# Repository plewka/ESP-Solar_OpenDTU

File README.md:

# ESP-Solar_OpenDTU
PCB for OpenDTU in Cable Branchbox, LineSupply w. Fuses, RS485/RS232-Olimex, Relais, DS2485 OneWire, I2C-Header...

Mechanically fits into quite compact HNS 989861-H01 wiring box (form closure only).
If not all features are used, even edged Wieland-Socket should fit.
LEDs need LightGuides: no. position-drawing and not included in material list 

Tradeoff: Very limited space, copyrighted code for ds2485

image::ESP-SolarV1.jpg

* WESP32-WROOM-based (internal or external antenna)

* 5x20 Fuseholder (Supply)
* Varistor
* HiLink Supplymodule f.e. 230V->3.3V

* 5x20 Fuseholder (Relais)
* Relais SANYOU 10A

* modern 1Wire-Controler DS2485
* programming Header (Shelly-Pinout)
* I2C+VCC+GND header
* 2x5 Ribbon Connector for Olimex' RS485/RS232-Modules
* LEDs (green: power, red:active, or:DS2485 GPIO)

* TTL serial connector f.e. for IR-Energy reading 
* robust cage clamps for external connections

The board was done for differend scenarios including HoymilesDTU, using different RF-Modules,
reading the new IR-Energy counters with "Volkszähler", measure distributed temerature locations 
with OneWire-Sensors and control of pool pump or heating elements, maybe some IR motion detection 
in the garage, interfacing RS485/Modbus/RS232 for Solar-Inverters etc. - CAN- and metering bus 
are missing, though.

Would be great to hear how you used it or modified it for!

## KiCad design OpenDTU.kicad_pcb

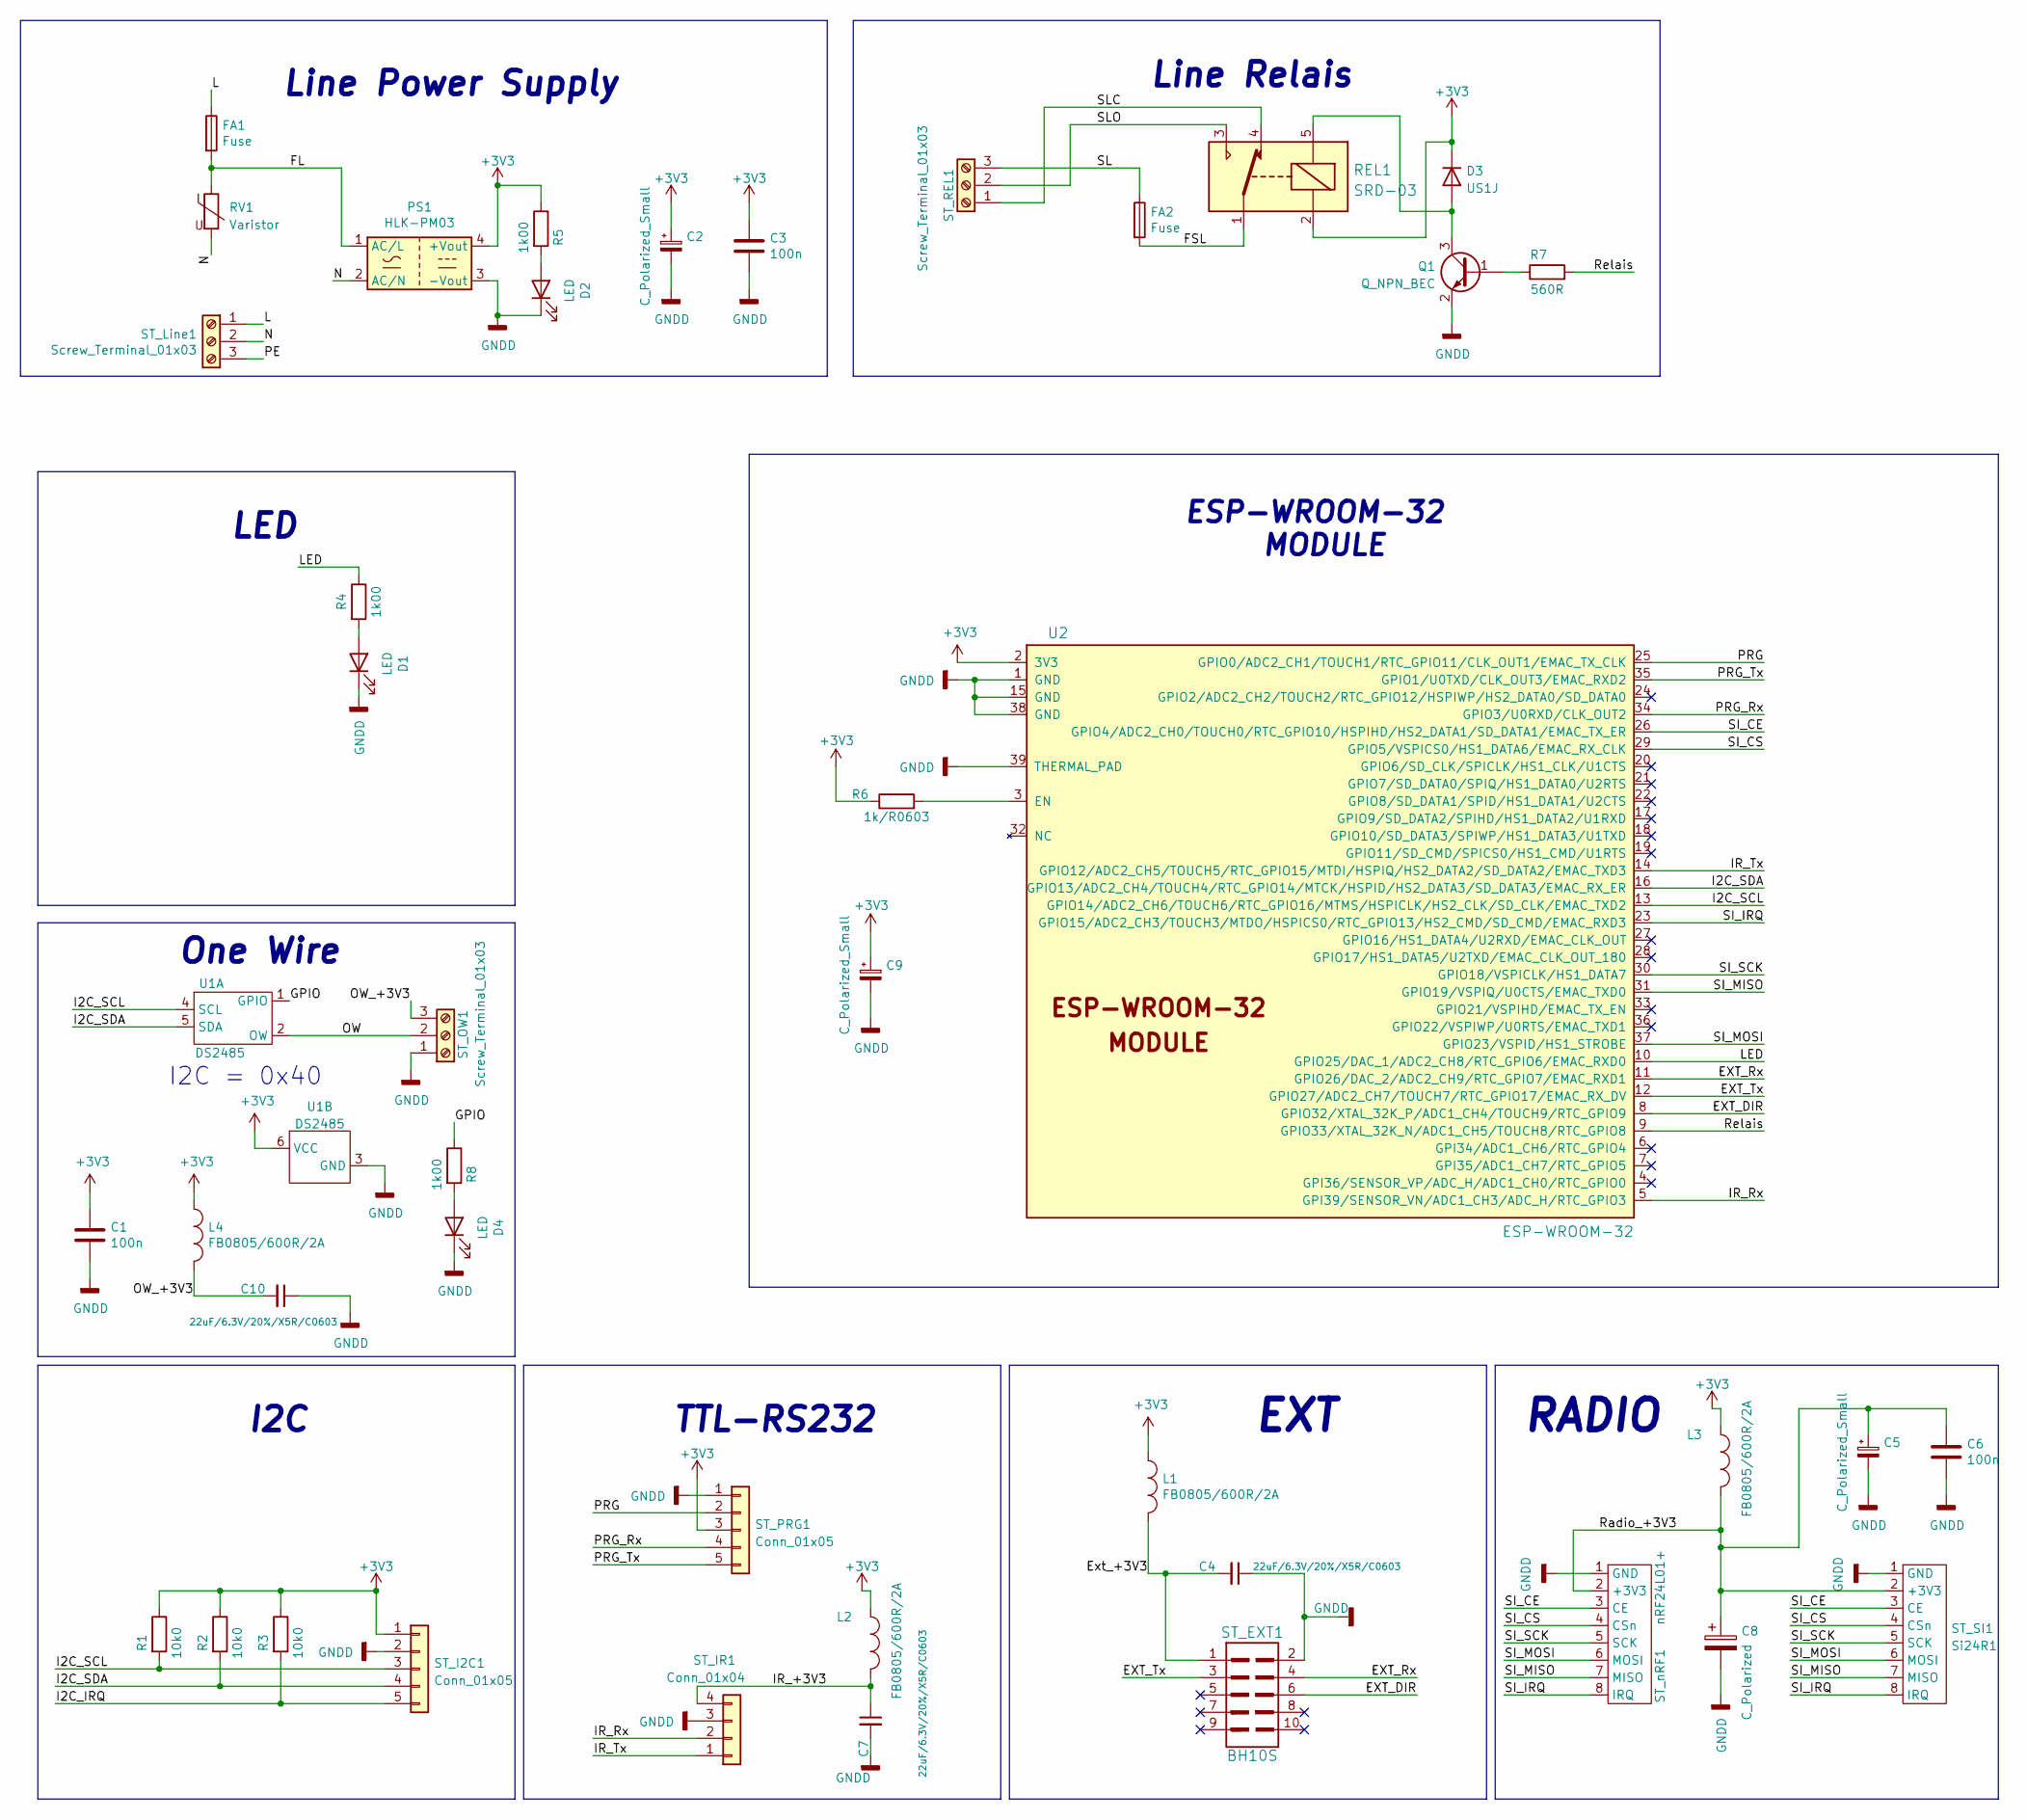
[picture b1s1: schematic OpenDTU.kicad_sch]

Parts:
C1, C3, C6: 100n; C_0603_1608Metric
C2, C5, C9: C_Polarized_Small; CP_EIA-3528-12_Kemet-T
C4, C7, C10: 22uF/6.3V/20%/X5R/C0603; C_0603_1608Metric
C8: C_Polarized; CP_EIA-7260-38_AVX-R
D1, D2, D4: LED; LED_D3.0mm_Clear
D3: US1J; D_SMA
FA1, FA2: Fuse; Fuseholder_Cylinder-5x20mm_Bulgin_FX0456_Vertical_Closed
L1, L2, L3, L4: FB0805/600R/2A; L_0805_2012Metric
PS1: HLK-PM03; Converter_ACDC_HiLink_HLK-PMxx
Q1: Q_NPN_BEC; SOT-23
R1, R2, R3: 10k0; R_0603_1608Metric
R4, R5, R8: 1k00; R_0603_1608Metric
R6: 1k/R0603; R_0603_1608Metric
R7: 560R; R_0603_1608Metric
REL1: SRD-03; Relay_SPDT_SANYOU_SRD_Series_Form_C
RV1: Varistor; RV_Disc_D12mm_W4.2mm_P7.5mm
ST_EXT1: BH10S; PinHeader_2x05_P2.54mm_Vertical
ST_I2C1: Conn_01x05; PinSocket_1x05_P2.54mm_Vertical
ST_IR1: Conn_01x04; TerminalBlock_WAGO_236-404_1x04_P5.00mm_45Degree
ST_Line1: Screw_Terminal_01x03; TerminalBlock_WAGO_236-403_1x03_P5.00mm_45Degree
ST_OW1: Screw_Terminal_01x03; TerminalBlock_WAGO_236-403_1x03_P5.00mm_45Degree
ST_PRG1: Conn_01x05; PinHeader_1x05_P2.54mm_Vertical
ST_REL1: Screw_Terminal_01x03; TerminalBlock_WAGO_236-403_1x03_P5.00mm_45Degree
ST_SI1: Si24R1; PinSocket_1x08_P1.27mm_Vertical
ST_nRF1: nRF24L01+; PinHeader_2x04_P2.54mm_Vertical
U1: DS2485; DFN-6-1EP_3x3mm_P0.95mm_EP1.7x2.6mm
U2: ESP-WROOM-32; ESP32-WROOM-32E

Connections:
+3V3: C1.1, C2.1, C3.1, C9.1, D3.1 (K), L1.1, L2.1, L3.1, L4.1, PS1.4 (+Vout), R1.1, R2.1, R3.1, R5.1, R6.1, REL1.2, ST_I2C1.1, ST_PRG1.3, U1.6 (VCC), U2.2 (3V3)
/EXT_DIR: ST_EXT1.6, U2.8 (GPIO32/XTAL_32K_P/ADC1_CH4/TOUCH9/RTC_G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)
/EXT_Rx: ST_EXT1.4, U2.11 (GPIO26/DAC_2/ADC2_CH9/RTC_GPIO7/EMAC_RX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)
/EXT_Tx: ST_EXT1.3, U2.12 (GPIO27/ADC2_CH7/TOUCH7/RTC_GPIO17/EMAC_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)
/Ext_+3V3: C4.2, L1.2, ST_EXT1.1
/FL: FA1.2, PS1.1 (AC/L), RV1.1
/FSL: FA2.2, REL1.1
/GPIO: R8.1, U1.1 (GPIO)
/I2C_IRQ: R3.2, ST_I2C1.5
/I2C_SCL: R1.2, ST_I2C1.3, U1.4 (SCL), U2.13 (GPIO14/ADC2_CH6/TOUCH6/RTC_GPIO16/MTMS/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)
/I2C_SDA: R2.2, ST_I2C1.4, U1.5 (SDA), U2.16 (GPIO13/ADC2_CH4/TOUCH4/RTC_GPIO14/MTCK/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)
/IR_+3V3: C7.1, L2.2, ST_IR1.4
/IR_Rx: ST_IR1.2, U2.5 (GPI39/SENSOR_VN/ADC1_CH3/ADC_H/RTC_GPIO3)
/IR_Tx: ST_IR1.1, U2.14 (GPIO12/ADC2_CH5/TOUCH5/RTC_GPIO15/MTDI/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)
/L: FA1.1, ST_Line1.1
/LED: R4.1, U2.10 (GPIO25/DAC_1/ADC2_CH8/RTC_GPIO6/EMAC_RX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)
/N: PS1.2 (AC/N), RV1.2, ST_Line1.2
/OW: ST_OW1.2, U1.2 (OW)
/OW_+3V3: C10.2, L4.2, ST_OW1.3
/PE: ST_Line1.3
/PRG: ST_PRG1.2, U2.25 (GPIO0/ADC2_CH1/TOUCH1/RTC_GPIO11/CLK_OU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)
/PRG_Rx: ST_PRG1.4, U2.34 (GPIO3/U0RXD/CLK_OUT2)
/PRG_Tx: ST_PRG1.5, U2.35 (GPIO1/U0TXD/CLK_OUT3/EMAC_RXD2)
/Radio_+3V3: C5.1, C6.1, C8.1, L3.2, ST_SI1.2 (+3V3), ST_nRF1.2 (+3V3)
/Relais: R7.2, U2.9 (GPIO33/XTAL_32K_N/ADC1_CH5/TOUCH8/RTC_G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)
/SI_CE: ST_SI1.3 (CE), ST_nRF1.3 (CE), U2.26 (GPIO4/ADC2_CH0/TOUCH0/RTC_GPIO10/HSPIHD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)
/SI_CS: ST_SI1.4 (CSn), ST_nRF1.4 (CSn), U2.29 (GPIO5/VSPICS0/HS1_DATA6/EMAC_RX_CLK)
/SI_IRQ: ST_SI1.8 (IRQ), ST_nRF1.8 (IRQ), U2.23 (GPIO15/ADC2_CH3/TOUCH3/MTDO/HSPICS0/RTC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)
/SI_MISO: ST_SI1.7 (MISO), ST_nRF1.7 (MISO), U2.31 (GPIO19/VSPIQ/U0CTS/EMAC_TXD0)
/SI_MOSI: ST_SI1.6 (MOSI), ST_nRF1.6 (MOSI), U2.37 (GPIO23/VSPID/HS1_STROBE)
/SI_SCK: ST_SI1.5 (SCK), ST_nRF1.5 (SCK), U2.30 (GPIO18/VSPICLK/HS1_DATA7)
/SL: FA2.1, ST_REL1.3
/SLC: REL1.4, ST_REL1.1
/SLO: REL1.3, ST_REL1.2
GNDD: C1.2, C2.2, C3.2, C4.1, C5.2, C6.2, C7.2, C8.2, C9.2, C10.1, D1.1 (K), D2.1 (K), D4.1 (K), PS1.3 (-Vout), Q1.2 (E), ST_EXT1.2, ST_I2C1.2, ST_IR1.3, ST_OW1.1, ST_PRG1.1, ST_SI1.1 (GND), ST_nRF1.1 (GND), U1.3 (GND), U2.1 (GND), U2.15 (GND), U2.38 (GND), U2.39 (THERMAL_PAD)
unnamed: D1.2 (A), R4.2
unnamed: D2.2 (A), R5.2
unnamed: D3.2 (A), Q1.3 (C), REL1.5
unnamed: D4.2 (A), R8.2
unnamed: Q1.1 (B), R7.1
unnamed: R6.2, U2.3 (EN)

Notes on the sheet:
I2C = 0x40
Line Relais
LED
EXT
ESP-WROOM-32 MODULE
RADIO
I2C
Line Power Supply
One Wire
TTL-RS232

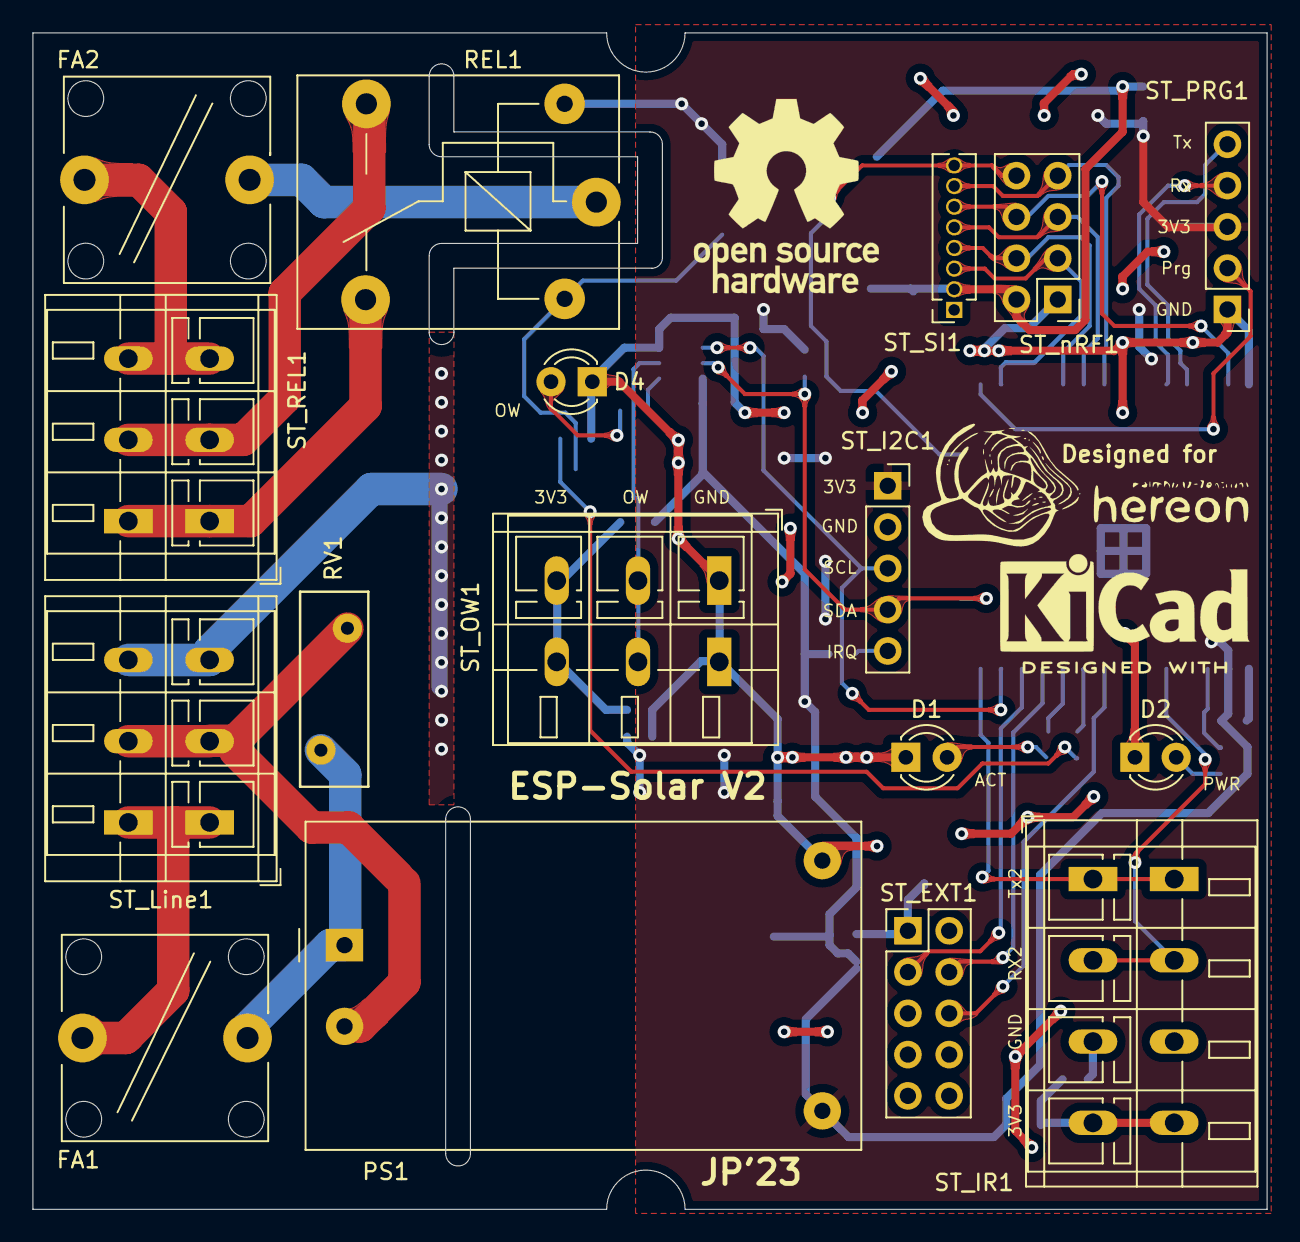
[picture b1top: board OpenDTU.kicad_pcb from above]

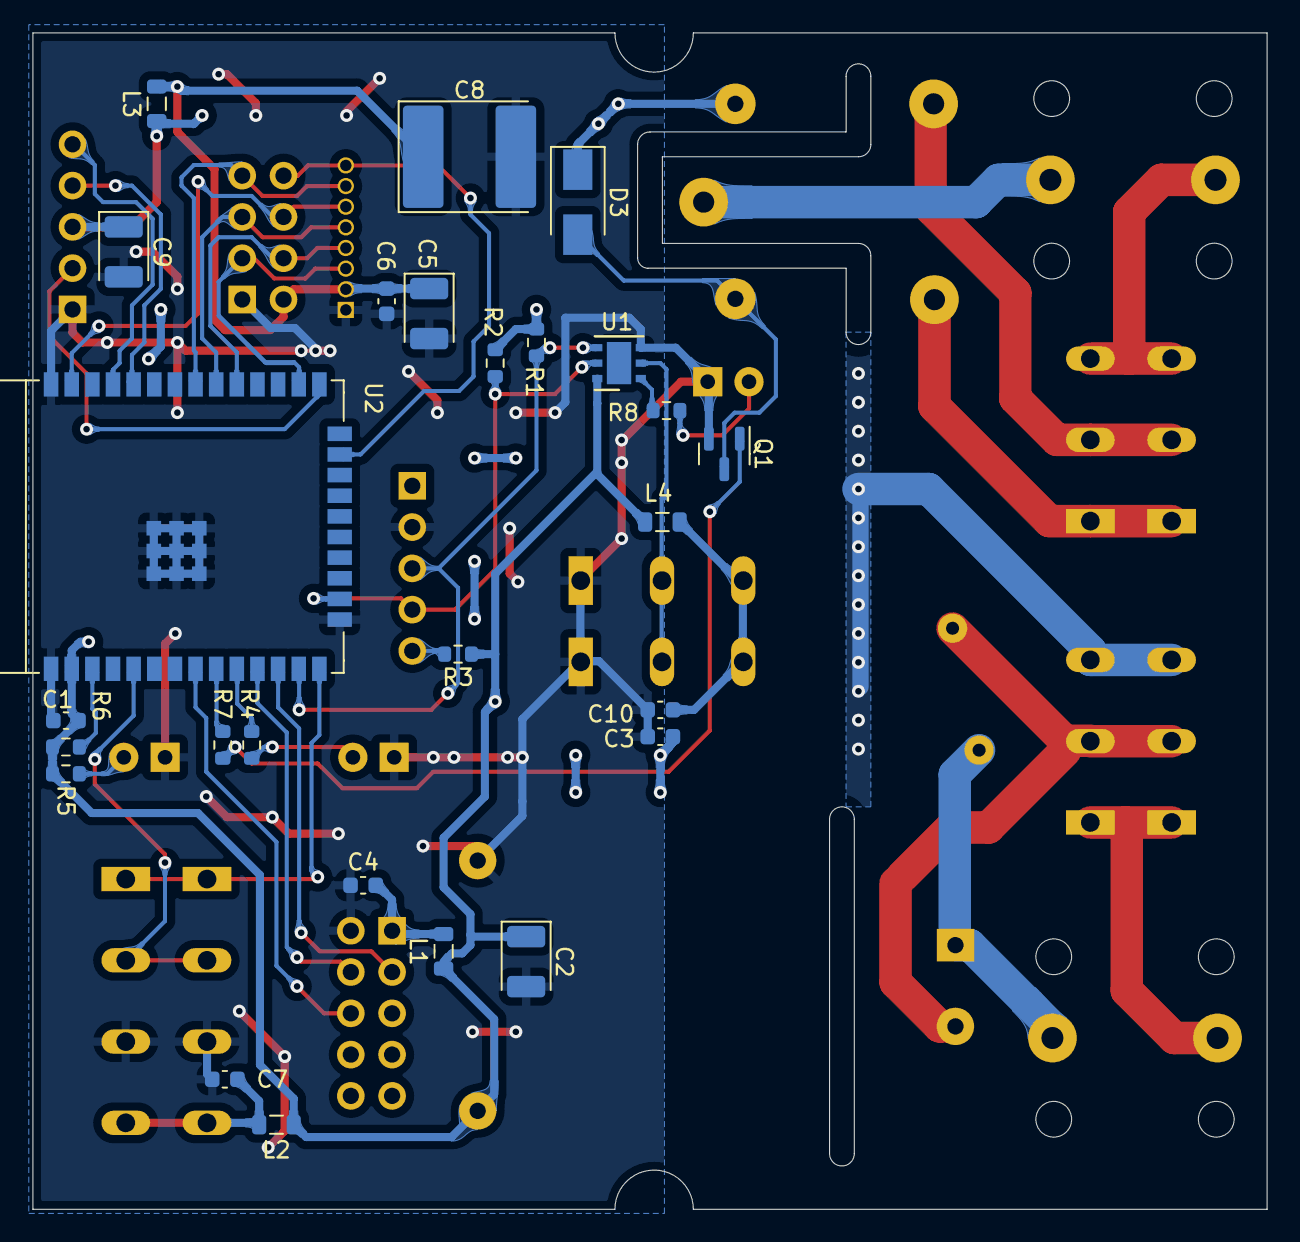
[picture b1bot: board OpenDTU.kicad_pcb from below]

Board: 2 copper layers, 75.9 x 72.4 mm, 43 parts (26 on the bottom side), 40 nets.

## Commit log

2023-01-15 Initial Upload, corrected V2
2023-01-15 V1 w/o OneWire
2023-01-15 Added image
2024-02-21 Update einleitung.adoc
    Hinweis zu OnBattery hinzugefügt
